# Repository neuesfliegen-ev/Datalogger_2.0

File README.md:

# 🛩️ Datalogger_2.0 

Datalogger for collecting, logging and transmitting RC flight data during the New Flying Competition
organised and held by the Neues Fliegen e.V.
Continuation of project Datalogger (first version)

---

## 🧩 Improvements

- Remove SIM card and use radio communication for telemetry
- Improve IMU sensor stability on flight
- Develop more efficient calibration process
- Develop a ground station capable of receiving and uploading live telemetry
- Implement FreeRTOS on ESP32

---

## 📦 Features

- Logs data to SD card in `.csv` format
- Captures:
  - 9-axis IMU data (acceleration, gyroscope, magnetometer)
  - Barometric pressure, altitude, and temperature
  - GPS coordinates, altitude, speed, and satellite count
- Streams telemetry to ground station through radio communication
- Ground station streams telemetry to web server
//to be refined

## 🧠 Core Components

| Component                  	| Description |
|-------------------------------|-------------|
| **ESP32**               		| Primary microcontroller |
| **WT-901B**         			  | 10-DOF IMU (acceleration, gyroscope, magnetometer + barometer)  |
| **GEP M10**               	| GEP-M10 GPS module utilizing the u-blox M10050 GPS chip |
| **Digital pitot sensor**    | PixHawk PX4 digital airspeed sensor |
| **E22-900T30D LoRa module**	| Enables the transmission of live telemetry via radio communication to ground station|
| **SD Card Module**        	| Stores `.csv` data logs |
//more to be added

---

## 🔧 Circuit Diagram
//to be added

---

## 👨‍💻 Credits

- Developed by the **Neues Fliegen e.V.** team
- Based on libraries by Arduino...

---

## 📷 License

- This project is shared publicly for educational and personal use only.
Commercial use or sale is not permitted without explicit permission
from Neues Fliegen e.V.
- see LICENSE file

---

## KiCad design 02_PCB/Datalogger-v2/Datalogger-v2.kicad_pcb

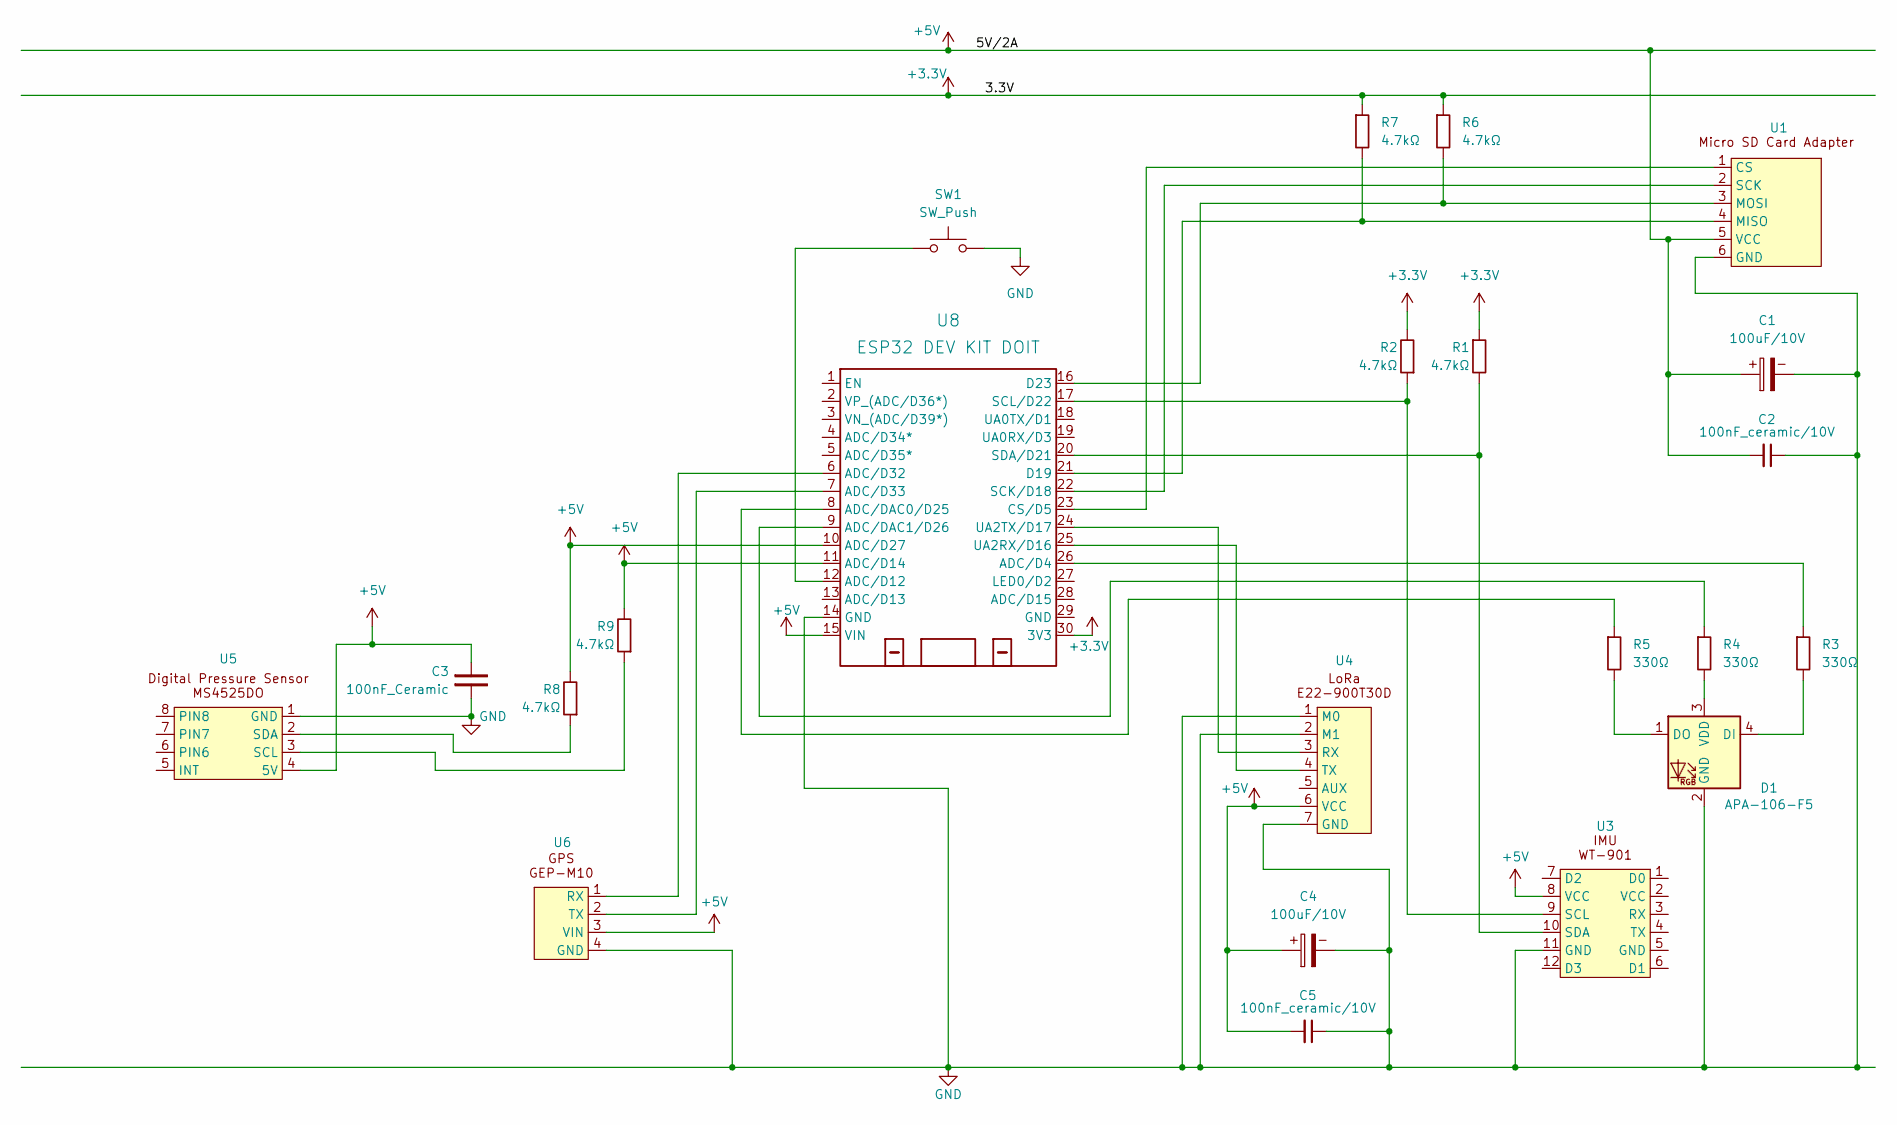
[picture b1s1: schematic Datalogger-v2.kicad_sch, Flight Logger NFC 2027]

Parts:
C1, C4: 100uF/10V; CP_Radial_D5.0mm_P2.50mm
C2, C5: 0.1uF_0603_16V; C_0805_2012Metric_Pad1.18x1.45mm_HandSolder; Part Number 0603YC104KAT2A; JLCPCB ID C14663
C3: 100nF_Ceramic; C_0805_2012Metric_Pad1.18x1.45mm_HandSolder
D1: APA-106-F5; LED_D5.0mm-4_RGB
R1, R2, R6, R7, R8, R9: 4.7kΩ; R_Axial_DIN0207_L6.3mm_D2.5mm_P10.16mm_Horizontal
R3, R4, R5: 330Ω; R_Axial_DIN0207_L6.3mm_D2.5mm_P10.16mm_Horizontal
SW1: SW_Push; SW_PUSH_6mm
U1: Micro SD Card Adapter; Micro_SD_Adapter
U3: WT901B
U4: E22-900T30D
U5: MS4525DO
U6: GPS GEP-M10
U8: ESP32 DEV KIT DOIT; DOIT-ESP32-DEVKIT-V1

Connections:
+3.3V: R1.1, R2.2, R6.1, R7.1, U8.30 (3V3)
+5V: C1.1, C2.2, C3.1, C4.1, C5.2, R8.2, R9.2, U1.5 (VCC), U3.8 (VCC), U4.6 (VCC), U5.4 (5V), U6.3 (VIN), U8.10 (ADC/D27), U8.11 (ADC/D14), U8.15 (VIN)
GND: C1.2, C2.1, C3.2, C4.2, C5.1, D1.2 (GND), SW1.2, U1.6 (GND), U3.11 (GND), U4.1 (M0), U4.2 (M1), U4.7 (GND), U5.1 (GND), U6.4 (GND), U8.14 (GND)
unnamed: D1.4 (DI), R3.2
unnamed: D1.1 (DO), R5.2
unnamed: D1.3 (VDD), R4.2
unnamed: U1.1 (CS), U8.23 (CS/D5)
unnamed: R7.2, U1.4 (MISO), U8.21 (D19)
unnamed: R6.2, U1.3 (MOSI), U8.16 (D23)
unnamed: U1.2 (SCK), U8.22 (SCK/D18)
unnamed: R2.1, U3.9 (SCL), U8.17 (SCL/D22)
unnamed: R1.2, U3.10 (SDA), U8.20 (SDA/D21)
unnamed: U4.3 (RX), U8.24 (UA2TX/D17)
unnamed: U4.4 (TX), U8.25 (UA2RX/D16)
unnamed: R9.1, U5.3 (SCL)
unnamed: R8.1, U5.2 (SDA)
unnamed: U6.1 (RX), U8.6 (ADC/D32)
unnamed: U6.2 (TX), U8.7 (ADC/D33)
unnamed: R3.1, U8.26 (ADC/D4)
unnamed: SW1.1, U8.12 (ADC/D12)
unnamed: R5.1, U8.8 (ADC/DAC0/D25)
unnamed: R4.1, U8.9 (ADC/DAC1/D26)

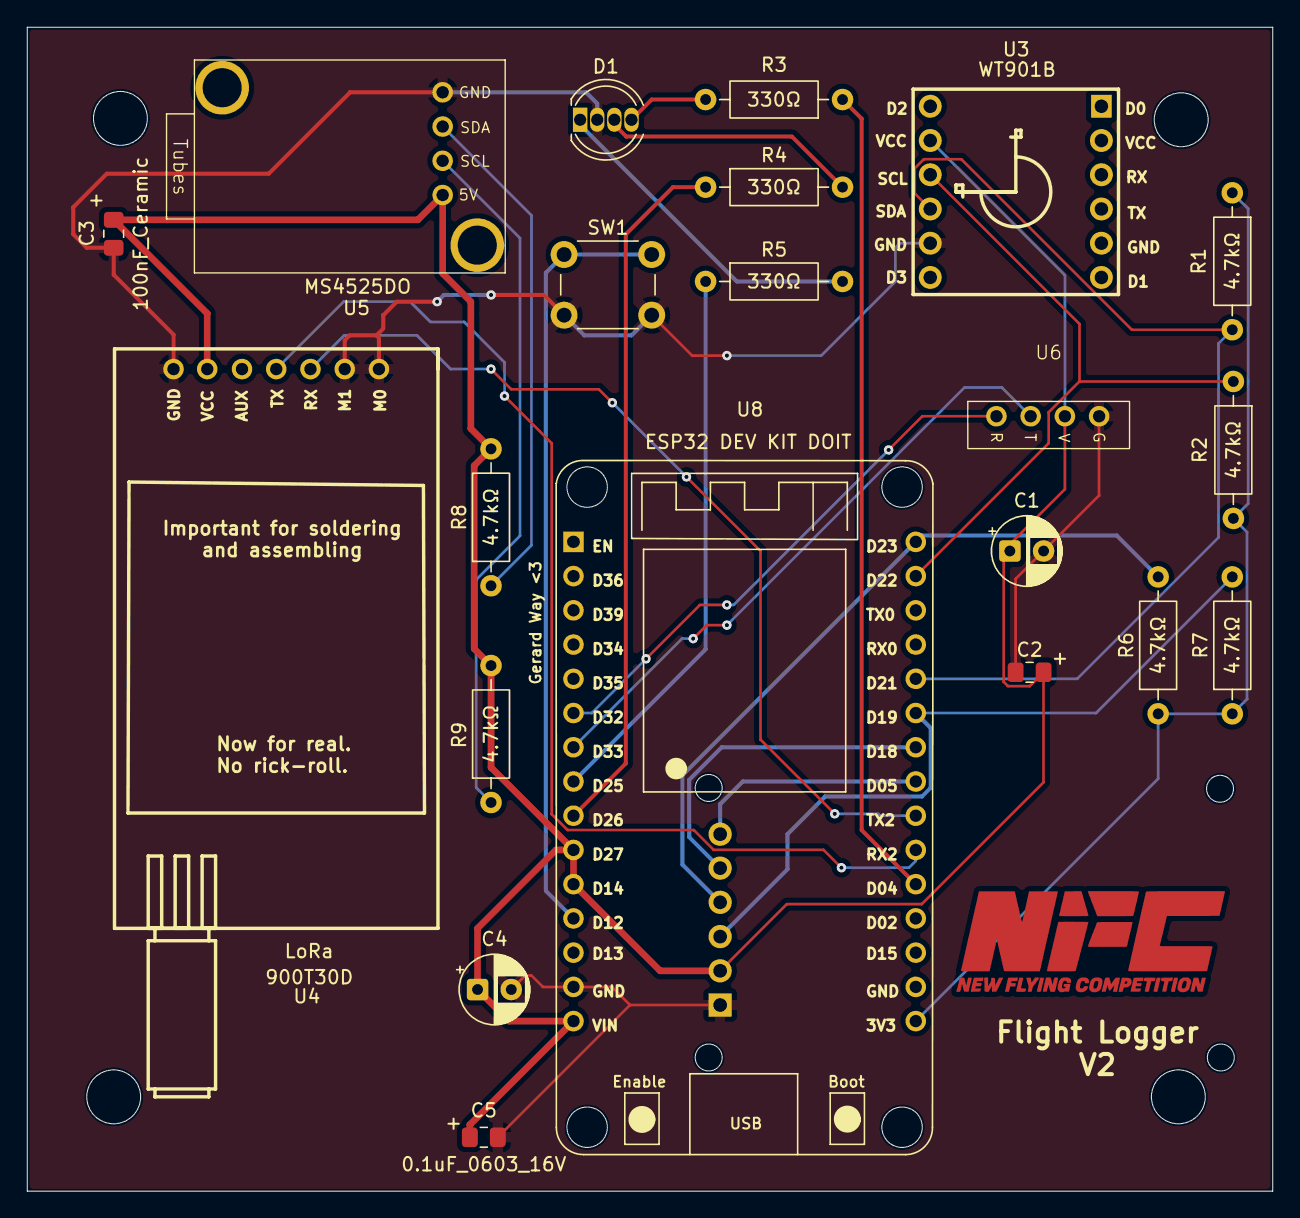
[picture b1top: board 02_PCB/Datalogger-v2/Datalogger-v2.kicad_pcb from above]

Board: 2 copper layers, 92.4 x 86.4 mm, 22 parts (1 on the bottom side), 22 nets.

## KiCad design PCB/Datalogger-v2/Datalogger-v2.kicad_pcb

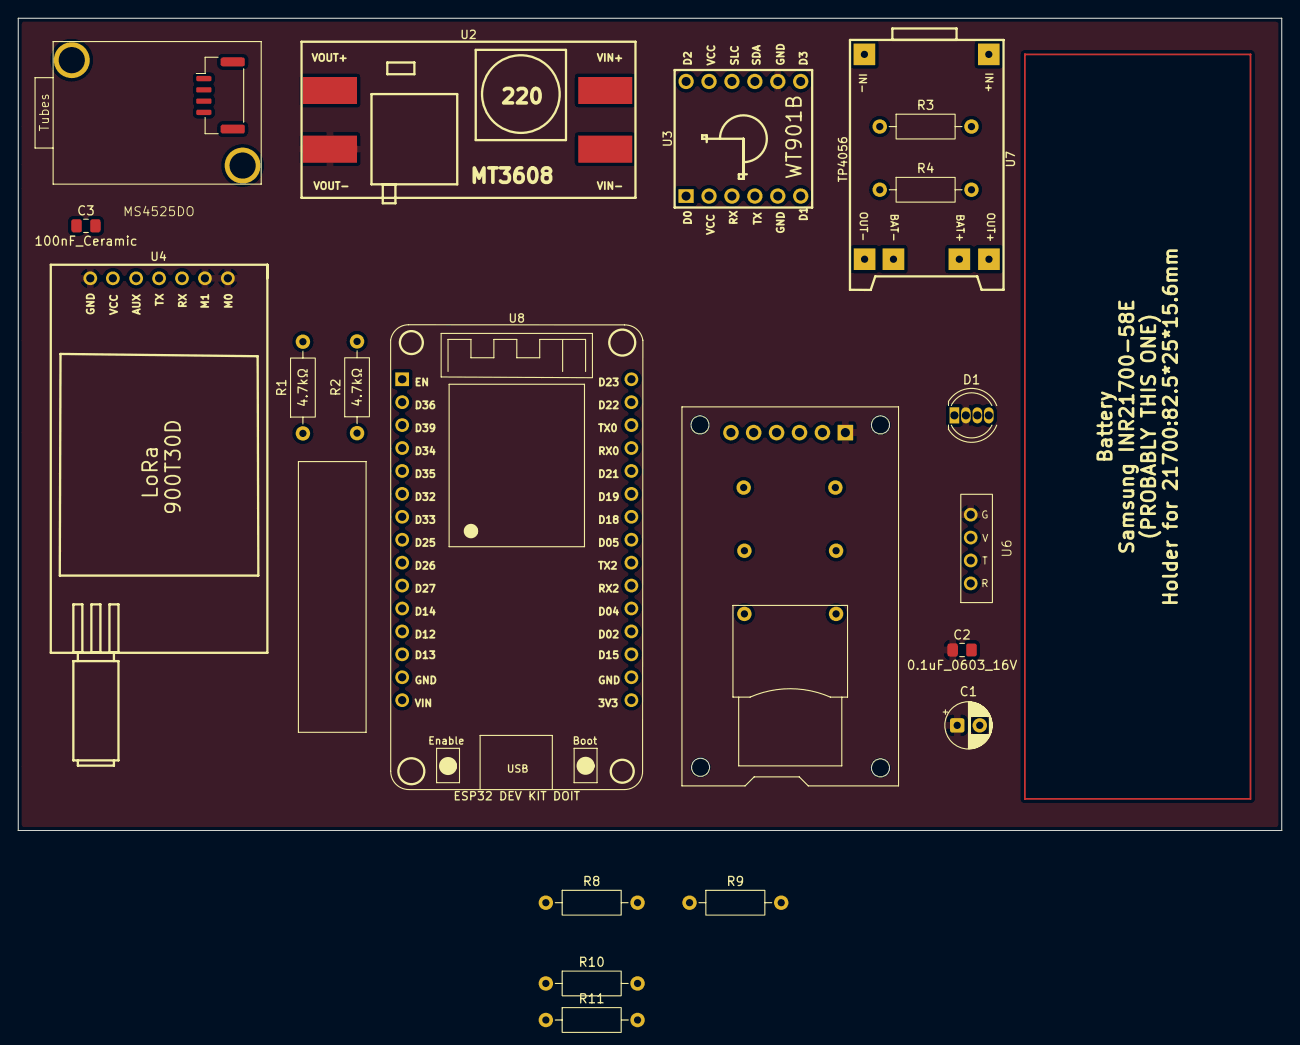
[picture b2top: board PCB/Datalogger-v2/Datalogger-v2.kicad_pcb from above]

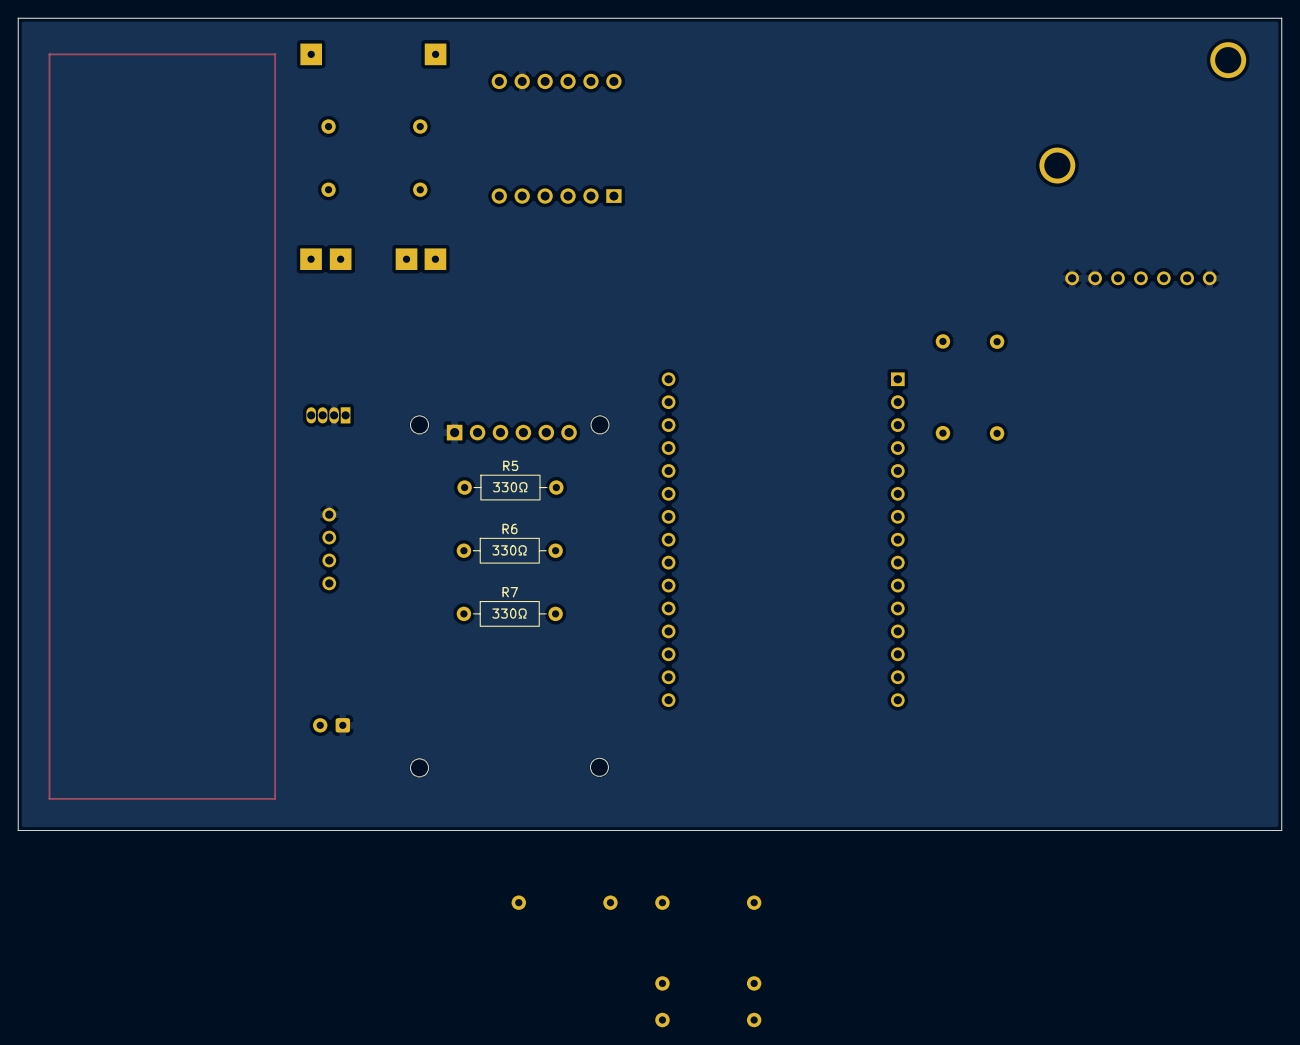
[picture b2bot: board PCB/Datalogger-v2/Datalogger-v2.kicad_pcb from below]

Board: 2 copper layers, 140.0 x 90.0 mm, 22 parts (3 on the bottom side), 16 nets, no tracks yet.

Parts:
C1: 100uF/10V; CP_Radial_D5.0mm_P2.50mm
C2: 0.1uF_0603_16V; C_0805_2012Metric_Pad1.18x1.45mm_HandSolder
C3: 100nF_Ceramic; C_0805_2012Metric_Pad1.18x1.45mm_HandSolder
D1: APA-106-F5; LED_D5.0mm-4_RGB
R1: 4.7kΩ; R_Axial_DIN0207_L6.3mm_D2.5mm_P10.16mm_Horizontal
R2: 4.7Ω; R_Axial_DIN0207_L6.3mm_D2.5mm_P10.16mm_Horizontal
R3, R4: Resistor; R_Axial_DIN0207_L6.3mm_D2.5mm_P10.16mm_Horizontal
R5, R6, R7: 330Ω; R_Axial_DIN0207_L6.3mm_D2.5mm_P10.16mm_Horizontal
R8, R9, R10, R11: 1kΩ; R_Axial_DIN0207_L6.3mm_D2.5mm_P10.16mm_Horizontal
U1: Micro SD Card Adapter; Micro_SD_Adapter
U2: MT3608
U3: WT901B
U4: E22-900T30D
U6: GPS GEP-M10
U7: TP4056
U8: ESP32 DEV KIT DOIT; DOIT-ESP32-DEVKIT-V1

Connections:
5V/2A: C1.2, C2.2, C3.1, R1.1, R2.2, R8.1, R9.1, R10.1, R11.1, U1.5 (VCC), U2.3 (VOUT+), U3.8 (VCC), U4.6 (VCC), U6.3 (VIN)
GND: C1.1, C2.1, D1.2 (GND), U1.6 (GND), U2.4 (VOUT-), U3.11 (GND), U4.1 (M0), U4.2 (M1), U4.7 (GND), U6.4 (GND)
unnamed: R4.2, U7.3 (B+)
unnamed: R3.2, U7.4 (B-)
unnamed: D1.4 (DI), R5.2
unnamed: D1.1 (DO), R7.2
unnamed: D1.3 (VDD), R6.2
unnamed: R11.2, U1.1 (CS)
unnamed: R9.2, U1.4 (MISO)
unnamed: R8.2, U1.3 (MOSI)
unnamed: R10.2, U1.2 (SCK)
unnamed: U2.1 (VIN+), U7.5 (OUT+)
unnamed: U2.2 (VIN-), U7.6 (OUT-)
unnamed: R2.1, U3.9 (SCL)
unnamed: R1.2, U3.10 (SDA)
unnamed: R3.1, R4.1, U8.3 (ADC/D13)

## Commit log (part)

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2025-10-18 Add LICENSE file with CC BY-NC 4.0 details
2025-10-18 Enhance README with project overview and features
    Expanded README with project details, features, and planned improvements.
2025-10-19 Update README with punctuation and features
2025-10-22 Test over
2025-10-22 Revert "Test over"
    This reverts commit 9dcfd34d027c08f30a68da4b73f85ede5e382057.
2025-10-22 Revert "Add files via upload"
    This reverts commit 9338cdd490b44a10897e920fde48f8d9d238c00d.
2025-10-23 Create github-best-practices.md
    github-best-practices.md was created to ensure everyone working with the repo are aware of the best practices to keep the repo clean and lean.
2025-10-23 Create branch-convention.md & misc change to github-best-practices.md
    - Created branch-convention.md to ensure everyone knows the rules for keeping our repo clean and avoiding conflicts.
    - Added a few aesthetic changes to github-best-practices.md
2025-10-29 Create aboutthisfolder.txt
    for arduino testing
2025-11-03 Revert "Repo/restructure"
2026-02-27 Manuals
    - IMU: WT901
    - Microcontroller: ESP32
    - Radio Module: E22-900T30D
2026-02-27 Manuals
    LiPo battery
2026-02-27 MT3608 Datasheet
    -Uploaded MT3608 datasheet
    -Renamed LoRa module datasheet
2026-03-06 Update pinout diagram
2026-03-12 Update sd_read2.ino
    adjusted log() and related functions to accept char arrays instead of String objects
2026-03-22 Create GPSandSD
2026-03-23 Update GPS and SD functions
    -Removed function declarations from cpp files
    -Added gps functions that can be called to return specific values
    -Implemented the use of gps date and time for creating filenames
2026-03-25 all files oof
    oooooffffff
2026-03-27 Implement Pitot sensor module
    - Implement Pitot class in Pitot.cpp and Pitot.h.
    - Add functions for differential pressure and airspeed calculation.
    - Initialize and handle raw I2C sensor readings with EMA filtering.
2026-03-29 replaced w fixed pointer passing
2026-04-01 add sublime file test (ignore)
2026-04-03 adding esp-idf project for testing
2026-04-20 Removed Arduino directory
    Unneeded
2026-04-20 Restructured repo
2026-04-20 Create README.md
    Everything for ground station
2026-04-21 working imu driver
2026-04-28 added telemetry and radio classes - incomplete, only for structure
2026-04-30 Test commit
2026-04-30 imu folder
2026-05-04 added com ports and bug fixes
2026-05-10 added airspeed sensor header files and cpp file
2026-05-13 radio stuff
2026-05-14 data.h files with the important quantities
2026-05-14 sending and receiving messages worked with this
2026-05-14 bug fixes
2026-05-15 Create PCB folder
2026-05-15 Create PCB directory
2026-05-15 Add schematic and PCB files
2026-05-20 gitignore: ignore unnecessary files
2026-05-20 comments: telemetry.h and telemetry.cpp
2026-05-20 comments: radio cpp and header file
2026-05-20 change files names to imu.h
2026-05-20 Change folder name to small letters
2026-05-20 Add 'modules' folder
2026-05-20 Add gitignore for changed folder
2026-05-20 Change folder name and structures
2026-05-20 changed to two tasks, one on each core; radio has a queue which gets filled instead of writing directly with uart_write_bytes() function
2026-05-21 Update PCB files
    - Add Libraries folder.
    - Update schematic.
    - Update PCB layout.
2026-05-26 deletions
2026-05-26 Edit .gitignore
2026-05-26 Update upto queue for radio in rtos
2026-05-29 adding sd card class dummy; still need to make double buffer + buffer queue for sd card writing and file naming function in main class. also separated setup and pins to another file
2026-05-30 finished sd card rough impelemntation and queue structure for logging task
2026-06-03 separated imu register file to prevent conflicts with global; bug fixes in gps and imu classes
2026-06-09 added airspeed sensor classes and updated Telemetry
2026-06-10 Update PCB schematic
2026-06-10 Update schematic and PCB files
    - Add symbol and footprint library.
2026-06-10 Update PCB file
    - Fix design rules
    - Add tracks
2026-06-14 Update PCB file
2026-06-15 Update schematic and PCB files
2026-06-22 sd card logging needs sd.end() (not only flush) !!!!
2026-06-23 Update schematic
2026-06-23 Update schematic and PCB layout
2026-06-25 Upload schematic screenshot
